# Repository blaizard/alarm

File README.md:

# Aube

Beautiful. Simple. Smart.

Aube is a smart alarm clock. It will guide you from the time you touch your bed until you wake up and is here make it a pleasant experience.
Aube is 3 major ideas: a design, a light and a smart device. 

## How to build Aube

The prototype is based on a Raspberry Pi 3 with the official 7 inches touch screen.
To fully build Aube, you will need a 3d printer, electronic circuit knowledges and some time!

The source contains various directories:
- **casing**: Contains the 3d models to be printed in order to build the skeleton of Aube
- **fw**: The firmware written in C to be compiled and loaded to a Microchip SAMD21 Microcontroller
- **schematics**: The electronics to handle the LED lighting with proximity sensor and the other sensors
- **sw**: The GUI of the alarm clock, written in Vanilla-Javascript and some back-end in Python

## Why Aube?
Pronounced /ob/, it is the translation of “dawn” in French. Dawn is a peaceful and relaxing experience which Aube is here to recreate every morning.

## Features
These are the raw features of Aube:
- Stereo speakers
- White LED light to simulate sunlight (with adjustable intensity and color temperature) with hovering dimming
- Connectivity: Wi-Fi, Bluetooth and USB ports (1xUSB type-C and 2x USB type-B) for charging only
- High sensitivity microphone for sleep monitoring
- Temperature, humidity and pressure sensors
- Proximity sensor to light up the screen on proximate movements

## Design
Inspired by Nordic designs, Aube is simple, pure with straight lines and strong contrasts.
Additionally, the user can customize the design by selecting the wooden base material.

3D modelization of the casing of Aube, this contains all the necessary electronics.

## Light
Our well-being and mood throughout the day is largely influenced by the light we are exposed to. Aube incorporates a light made to mimic the natural sun light.
Both intensity and light temperature can vary from 6500K to 4500K to recreate at best the color temperature of the light. Fade in from 4500K to 6500K in the morning to wake up smoothly and staying at 5000K in the evening to read a book before switching off the light.

The light has capacitive hovering capability, which means, without touching the device and by simply passing your hand on top of Aube, one can dim in or out the light.

Extract of the LED lighting circuitry.

## Apps
A set of Apps are displayed on the main screen of the alarm clock to provide the user with a personalized dashboard. The layout and the Apps can be selected by the user and configured to fit customized needs.

The following describes the default Apps coming with Aube. They all come with various designs that can be selected to create a personalized experience.

## Clock
The clock is the essential application for an alarm clock. It’s core functionality is to provide accurate time but also notify the user on important times or dates.

Alarms can trigger an action or a chain of actions, for example, it can be configured to slowly dimm in the LED lights and play a music through Spotify. Or open the blind and start your coffee machine… anything combination of operation is possible and configurable.

Actions can be:
- Dimm in/out the embedded LED light
- Speak out a predefined message
- Trigger actions from any Apps available (Spotify with the Music Apps, Meeting in the morning with the Calendar Apps…)
- IFTTT support to trigger up to 500+ services

## Sleep
Monitor your sleep using the integrated high sensitivity microphone. Can connect to sleep monitor devices for more accurate results.

It will also record your sleep (if you like), and give you insights (if you woke up, moved or even snored) during your sleep.

## Weather
Give you up to date information of the local weather. It can also provide you with the right forecast for the day when combined with the alarm. Or simply configured to give you the next 5 days forecast for your next vacations trip.
In addition, the weather Apps connects to internal sensors to give you current and accurate information about the pressure, humidity, luminosity and temperature of the room.

## Calendar
Connected to your personal calendar, it will inform you about your next meetings in the morning, to make sure you never miss any of your appointments!

## News
Aube will inform you of the main news every morning or RSS feed you connect it too. I can also read you a digest of the news every morning as you wake up.

## Music
Connect it to your favorite music provider: Spotify, … and it will wake you up with your favorite playlist in the morning.

## Radio
The radio Apps can connect to any digital radio or podcasts through the web to give you the right information in the morning or before you go to bed.

## Baby Monitor
Check if your baby is sleeping well with the Baby Monitor. It connects to your third party wireless camera or baby monitor to give you the information you need to ensure your peace of mind before you fall asleep.

## Countdown
Cannot wait for your next vacation? Your birthday? or your old friend coming to town? The countdown Apps will inform you about the remaining days before an event happen.

# Phone charging
In addition, Aube comes with USB ports on the back made to charge your phone. Equipped with USB Type-B and the new USB Type-C port, you should not need any other piece of electronics on your night stand anymore.

# Open Source Framework
All Apps are built on a fixed but powerful API (Application Programming Interface). This enables anyone to interact with the core functionality of Aube and hence develop compatible applications. Opening Aube to developers brings unlimited possibilities.

The process is simple, one needs to download the SDK (Software Development Kit), and follow the tutorial to develop its own application.

The application development is extremely simple in order to give anyone the possibility to develop its own Apps. In addition, applications are developed in the most predominant programming language (Javascript) and hence can be coupled with a variety of existing modules to speed up development.

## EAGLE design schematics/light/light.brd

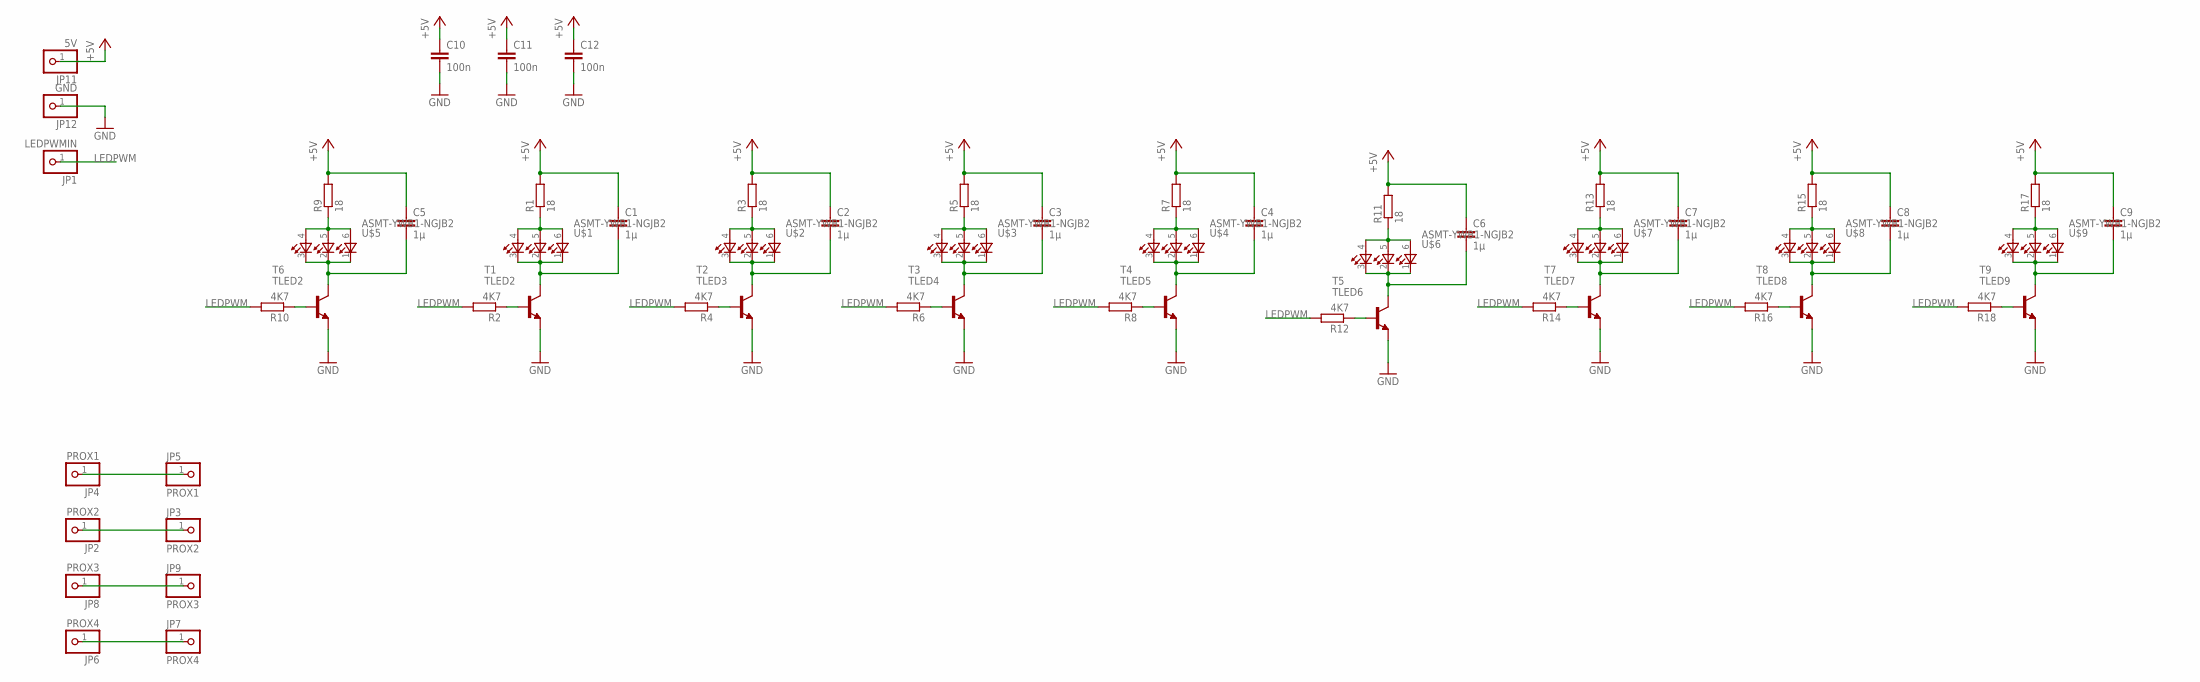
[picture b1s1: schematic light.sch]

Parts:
C1, C2, C3, C4, C5, C6, C7, C8, C9: 1µ; C0805
C10, C11, C12: 100n; C0805
JP1: LEDPWMIN; 1X01
JP2, JP3: PROX2; 1X01
JP4, JP5: PROX1; 1X01
JP6, JP7: PROX4; 1X01
JP8, JP9: PROX3; 1X01
JP11: 5V; 1X01
JP12: GND; 1X01
R1, R3, R5, R7, R9, R11, R13, R15, R17: 18; R0805
R2, R4, R6, R8, R10, R12, R14, R16, R18: 4K7; R0805
T1, T6: TLED2; SOT23-BEC
T2: TLED3; SOT23-BEC
T3: TLED4; SOT23-BEC
T4: TLED5; SOT23-BEC
T5: TLED6; SOT23-BEC
T7: TLED7; SOT23-BEC
T8: TLED8; SOT23-BEC
T9: TLED9; SOT23-BEC
U$1, U$2, U$3, U$4, U$5, U$6, U$7, U$8, U$9: ASMT-YWB1-NGJB2

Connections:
+5V: C1.1, C2.1, C3.1, C4.1, C5.1, C6.1, C7.1, C8.1, C9.1, C10.1, C11.1, C12.1, JP11.1, R1.2, R3.2, R5.2, R7.2, R9.2, R11.2, R13.2, R15.2, R17.2
BASE2: R12.1, T5.B
BASE3: R14.1, T7.B
BASE4: R16.1, T8.B
BASE5: R18.1, T9.B
COLLECTOR2: C6.2, T5.C, U$6.1, U$6.2, U$6.3
COLLECTOR3: C7.2, T7.C, U$7.1, U$7.2, U$7.3
COLLECTOR4: C8.2, T8.C, U$8.1, U$8.2, U$8.3
COLLECTOR5: C9.2, T9.C, U$9.1, U$9.2, U$9.3
GND: C10.2, C11.2, C12.2, JP12.1, T1.E, T2.E, T3.E, T4.E, T5.E, T6.E, T7.E, T8.E, T9.E
LEDPWM: JP1.1, R2.2, R4.2, R6.2, R8.2, R10.2, R12.2, R14.2, R16.2, R18.2
unnamed: R1.1, U$1.4, U$1.5, U$1.6
unnamed: C1.2, T1.C, U$1.1, U$1.2, U$1.3
unnamed: C2.2, T2.C, U$2.1, U$2.2, U$2.3
unnamed: R3.1, U$2.4, U$2.5, U$2.6
unnamed: R2.1, T1.B
unnamed: R4.1, T2.B
unnamed: C3.2, T3.C, U$3.1, U$3.2, U$3.3
unnamed: R5.1, U$3.4, U$3.5, U$3.6
unnamed: R6.1, T3.B
unnamed: C4.2, T4.C, U$4.1, U$4.2, U$4.3
unnamed: R7.1, U$4.4, U$4.5, U$4.6
unnamed: R8.1, T4.B
unnamed: R11.1, U$6.4, U$6.5, U$6.6
unnamed: C5.2, T6.C, U$5.1, U$5.2, U$5.3
unnamed: R13.1, U$7.4, U$7.5, U$7.6
unnamed: R15.1, U$8.4, U$8.5, U$8.6
unnamed: R17.1, U$9.4, U$9.5, U$9.6
unnamed: JP2.1, JP3.1
unnamed: JP4.1, JP5.1
unnamed: JP6.1, JP7.1
unnamed: JP8.1, JP9.1
unnamed: R9.1, U$5.4, U$5.5, U$5.6
unnamed: R10.1, T6.B

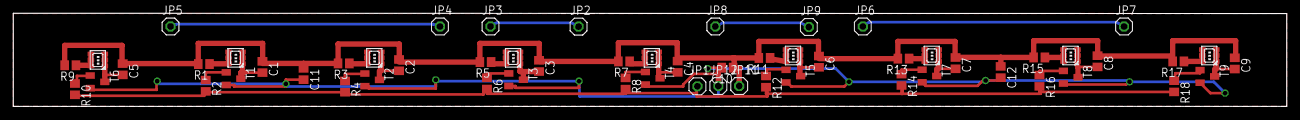
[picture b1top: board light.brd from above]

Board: 2 copper layers, 192.0 x 14.0 mm, 59 parts (0 on the bottom side), 34 nets.

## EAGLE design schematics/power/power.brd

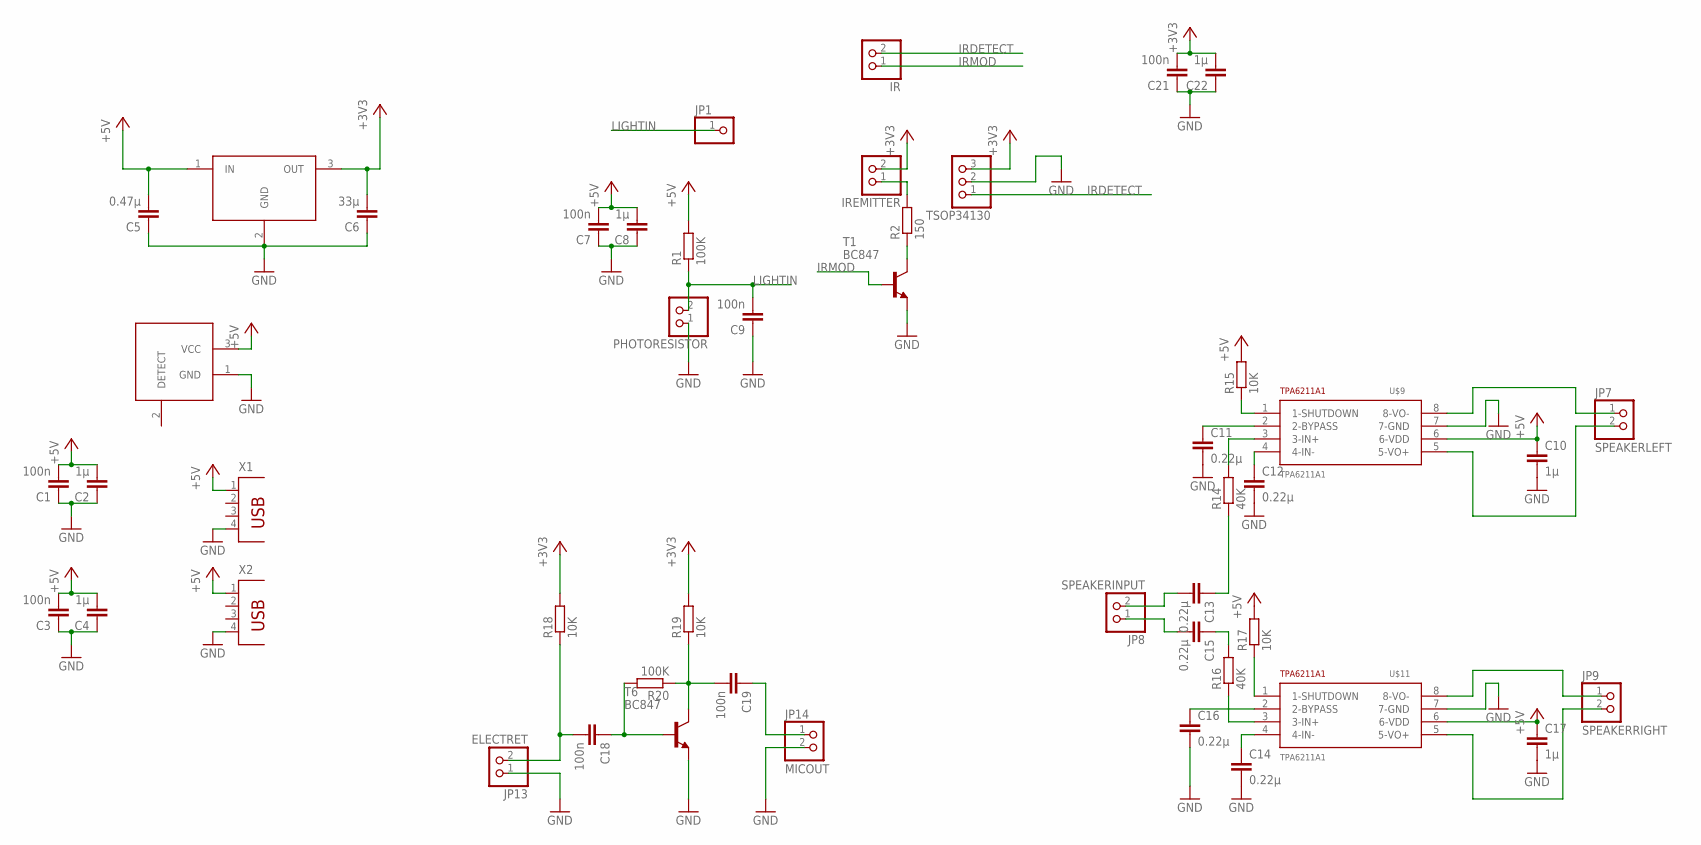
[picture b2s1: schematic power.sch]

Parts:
C1, C3, C7, C9, C18, C19, C21: 100n; C0805
C2, C4, C8, C10, C17, C22: 1µ; C0805
C5: 0.47µ; C0805
C6: 33µ; C0805
C11, C12, C13, C14, C15, C16: 0.22µ; C0805
IR: PINHD-1X2; 1X02
IREMITTER: PINHD-1X2; 1X02
JP1: PINHD-1X1; 1X01
JP7: SPEAKERLEFT; 1X02
JP8: SPEAKERINPUT; 1X02
JP9: SPEAKERRIGHT; 1X02
JP13: ELECTRET; 1X02
JP14: MICOUT; 1X02
PHOTORESISTOR: PINHD-1X2; 1X02
R1, R20: 100K; R0805
R2: 150; R0805
R14, R16: 40K; R0805
R15, R17, R18, R19: 10K; R0805
T1, T6: BC847; SOT23
TSOP34130: PINHD-1X3; 1X03
U$1: LM3940IMP-3.3; SOT223
U$2: POWERPLUG; DC10LPSOCKET
U$9, U$11: TPA6211A1; MSOP8
X1, X2: PN87520

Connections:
+3V3: C6.2, C21.2, C22.2, IREMITTER.2, R18.2, R19.2, TSOP34130.3, U$1.3 (OUT)
+5V: C1.2, C2.2, C3.2, C4.2, C5.2, C7.2, C8.2, C10.1, C17.1, R1.2, R15.2, R17.2, U$1.1 (IN), U$2.3 (VCC), U$9.6 (6-VDD), U$11.6 (6-VDD), X1.1, X2.1
GND: C1.1, C2.1, C3.1, C4.1, C5.1, C6.1, C7.1, C8.1, C9.1, C10.2, C11.2, C12.2, C14.2, C16.2, C17.2, C21.1, C22.1, JP13.1, JP14.2, PHOTORESISTOR.1, T1.2 (E), T6.2 (E), TSOP34130.2, U$1.2 (GND), U$2.1 (GND), U$9.7 (7-GND), U$11.7 (7-GND), X1.4, X2.4
IRDETECT: IR.2, TSOP34130.1
IRMOD: IR.1, T1.1 (B)
LIGHTIN: C9.2, JP1.1, PHOTORESISTOR.2, R1.1
unnamed: IREMITTER.1, R2.2
unnamed: R2.1, T1.3 (C)
unnamed: C13.1, R14.1
unnamed: C13.2, JP8.2
unnamed: JP7.1, U$9.8 (8-VO-)
unnamed: JP7.2, U$9.5 (5-VO+)
unnamed: C11.1, U$9.2 (2-BYPASS)
unnamed: C12.1, U$9.4 (4-IN-)
unnamed: R14.2, U$9.3 (3-IN+)
unnamed: C15.2, JP8.1
unnamed: C15.1, R16.2
unnamed: R15.1, U$9.1 (1-SHUTDOWN)
unnamed: R16.1, U$11.3 (3-IN+)
unnamed: C14.1, U$11.4 (4-IN-)
unnamed: C16.1, U$11.2 (2-BYPASS)
unnamed: R17.1, U$11.1 (1-SHUTDOWN)
unnamed: JP9.1, U$11.8 (8-VO-)
unnamed: JP9.2, U$11.5 (5-VO+)
unnamed: C19.2, R19.1, R20.1, T6.3 (C)
unnamed: C18.1, R20.2, T6.1 (B)
unnamed: C18.2, JP13.2, R18.1
unnamed: C19.1, JP14.1

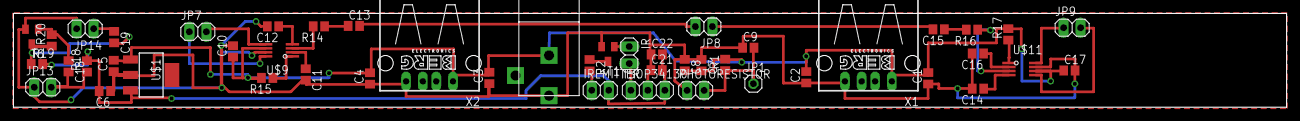
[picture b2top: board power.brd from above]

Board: 2 copper layers, 190.0 x 14.0 mm, 48 parts (0 on the bottom side), 28 nets.

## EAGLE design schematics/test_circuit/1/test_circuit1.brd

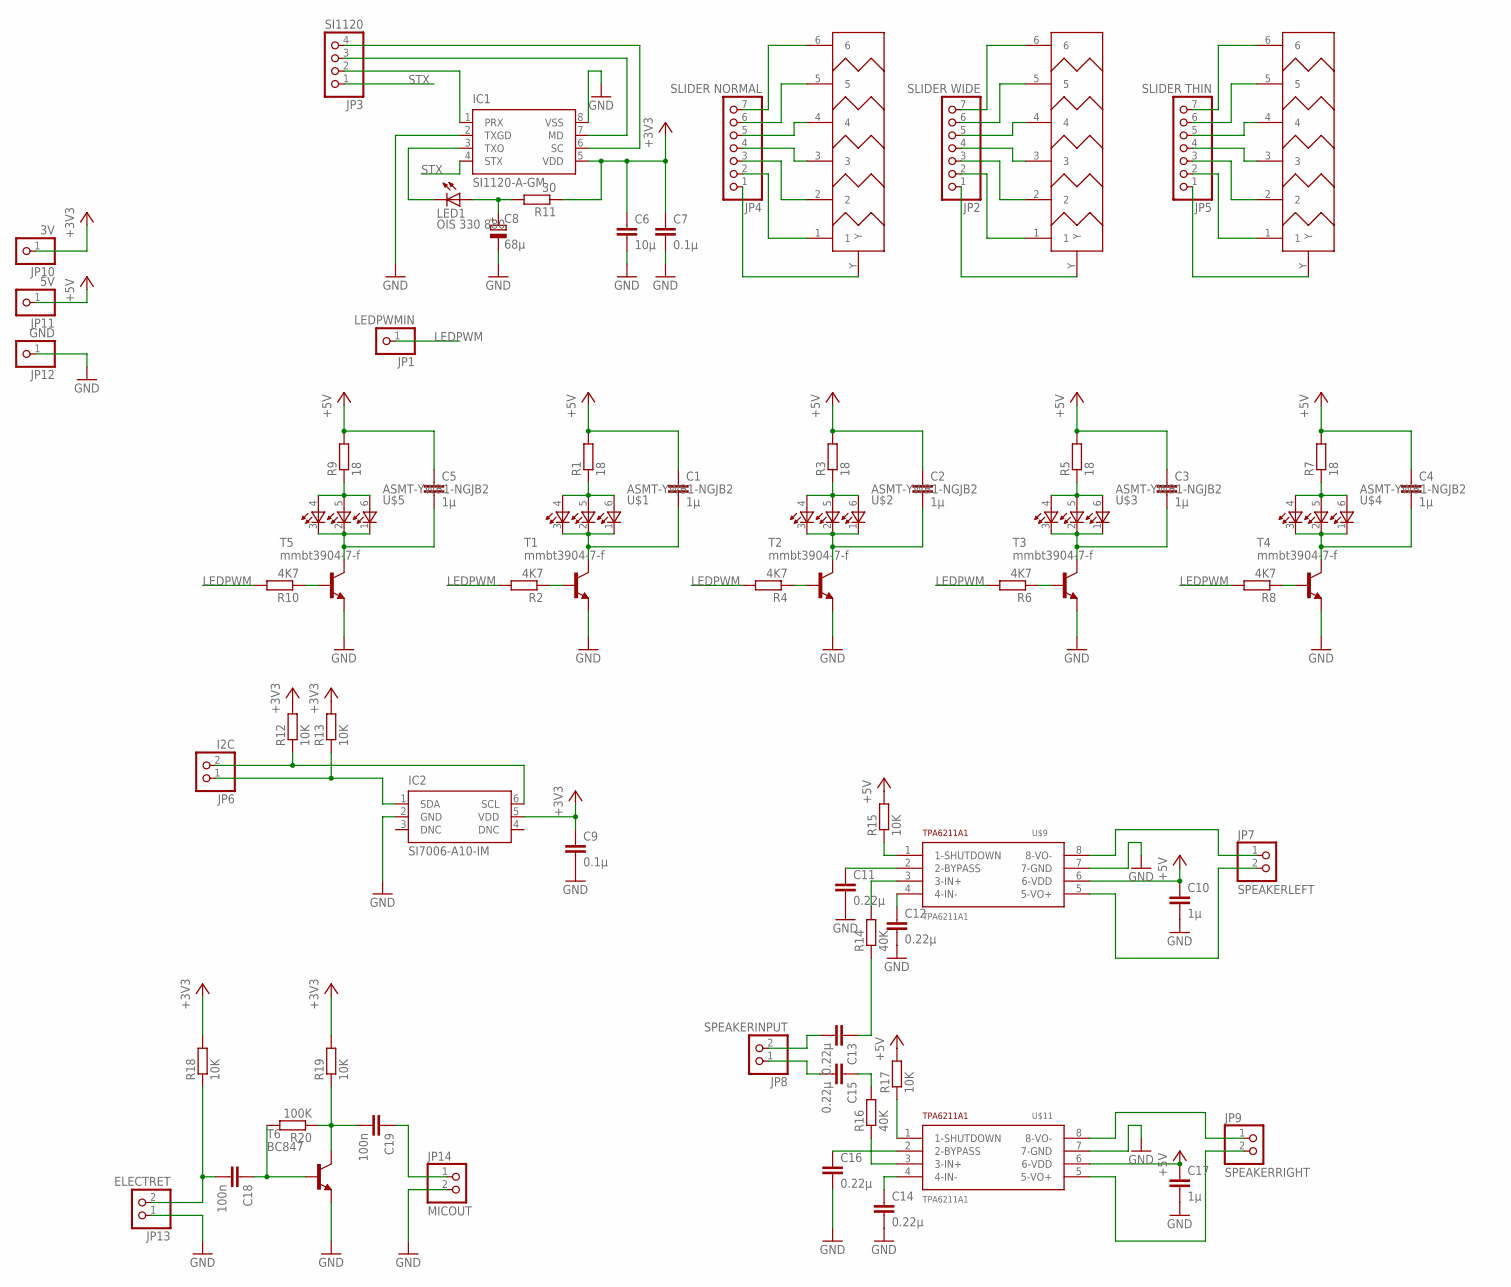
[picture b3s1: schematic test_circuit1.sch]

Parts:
C1, C2, C3, C4, C5, C10, C17: 1µ; C0805
C6: 10µ; C0805
C7, C9: 0.1µ; C0805
C8: 68µ; E2,5-7
C11, C12, C13, C14, C15, C16: 0.22µ; C0805
C18, C19: 100n; C0805
IC1: SI1120-A-GM; ODFN8-3X3
IC2: SI7006-A10-IM; DFN6-3X3
JP1: LEDPWMIN; 1X01
JP2: SLIDER WIDE; 1X07
JP3: SI1120; 1X04
JP4: SLIDER NORMAL; 1X07
JP5: SLIDER THIN; 1X07
JP6: I2C; 1X02
JP7: SPEAKERLEFT; 1X02
JP8: SPEAKERINPUT; 1X02
JP9: SPEAKERRIGHT; 1X02
JP10: 3V; 1X01
JP11: 5V; 1X01
JP12: GND; 1X01
JP13: ELECTRET; 1X02
JP14: MICOUT; 1X02
LED1: OIS 330 880; SML1206
R1, R3, R5, R7, R9: 18; R0805
R2, R4, R6, R8, R10: 4K7; R0805
R11: 30; R0805
R12, R13, R15, R17, R18, R19: 10K; R0805
R14, R16: 40K; R0805
R20: 100K; R0805
T1, T2, T3, T4, T5: mmbt3904-7-f; SOT23-EBC
T6: BC847; SOT23
U$1, U$2, U$3, U$4, U$5: ASMT-YWB1-NGJB2
U$6: SLIDER160MM_RESINT; SLIDER160MM_RI
U$7: SLIDER16MM_RESINT_WIDEY; SLIDER160MM_RI_WIDERY
U$8: SLIDER160MM_RESINT_THIN; SLIDER160MM_RI_THIN
U$9, U$11: TPA6211A1; MSOP8

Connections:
+3V3: C6.1, C7.1, C9.1, IC1.5 (VDD), IC2.5 (VDD), JP10.1, R11.1, R12.2, R13.2, R18.2, R19.2
+5V: C1.1, C2.1, C3.1, C4.1, C5.1, C10.1, C17.1, JP11.1, R1.2, R3.2, R5.2, R7.2, R9.2, R15.2, R17.2, U$9.6 (6-VDD), U$11.6 (6-VDD)
GND: C6.2, C7.2, C8.-, C9.2, C10.2, C11.2, C12.2, C14.2, C16.2, C17.2, IC1.2 (TXGD), IC1.8 (VSS), IC2.2 (GND), JP12.1, JP13.1, JP14.2, T1.E, T2.E, T3.E, T4.E, T5.E, T6.2 (E), U$9.7 (7-GND), U$11.7 (7-GND)
LEDPWM: JP1.1, R2.2, R4.2, R6.2, R8.2, R10.2
unnamed: R1.1, U$1.4, U$1.5, U$1.6
unnamed: C1.2, T1.C, U$1.1, U$1.2, U$1.3
unnamed: C2.2, T2.C, U$2.1, U$2.2, U$2.3
unnamed: R3.1, U$2.4, U$2.5, U$2.6
unnamed: R2.1, T1.B
unnamed: R4.1, T2.B
unnamed: C3.2, T3.C, U$3.1, U$3.2, U$3.3
unnamed: R5.1, U$3.4, U$3.5, U$3.6
unnamed: R6.1, T3.B
unnamed: C4.2, T4.C, U$4.1, U$4.2, U$4.3
unnamed: R7.1, U$4.4, U$4.5, U$4.6
unnamed: R8.1, T4.B
unnamed: C5.2, T5.C, U$5.1, U$5.2, U$5.3
unnamed: R9.1, U$5.4, U$5.5, U$5.6
unnamed: R10.1, T5.B
unnamed: JP4.7, U$6.6
unnamed: JP4.6, U$6.5
unnamed: JP4.5, U$6.4
unnamed: JP4.4, U$6.3
unnamed: JP4.3, U$6.2
unnamed: JP4.2, U$6.1
unnamed: IC1.3 (TXO), LED1.C
unnamed: C8.+, LED1.A, R11.2
unnamed: IC1.7 (MD), JP3.3
unnamed: IC1.6 (SC), JP3.4
unnamed: IC1.1 (PRX), JP3.2
unnamed: JP4.1, U$6.Y
unnamed: JP2.7, U$7.6
unnamed: JP2.6, U$7.5
unnamed: JP2.5, U$7.4
unnamed: JP2.4, U$7.3
unnamed: JP2.3, U$7.2
unnamed: JP2.2, U$7.1
unnamed: JP2.1, U$7.Y
unnamed: JP5.7, U$8.6
unnamed: JP5.6, U$8.5
unnamed: JP5.5, U$8.4
unnamed: JP5.4, U$8.3
unnamed: JP5.3, U$8.2
unnamed: JP5.2, U$8.1
unnamed: JP5.1, U$8.Y
unnamed: C13.1, R14.1
unnamed: C13.2, JP8.2
unnamed: IC2.6 (SCL), JP6.2, R12.1
unnamed: IC2.1 (SDA), JP6.1, R13.1
unnamed: JP7.1, U$9.8 (8-VO-)
unnamed: JP7.2, U$9.5 (5-VO+)
unnamed: C11.1, U$9.2 (2-BYPASS)
unnamed: C12.1, U$9.4 (4-IN-)
unnamed: R14.2, U$9.3 (3-IN+)
unnamed: C15.2, JP8.1
unnamed: C15.1, R16.2
unnamed: R15.1, U$9.1 (1-SHUTDOWN)
unnamed: R16.1, U$11.3 (3-IN+)
unnamed: C14.1, U$11.4 (4-IN-)
unnamed: C16.1, U$11.2 (2-BYPASS)
unnamed: R17.1, U$11.1 (1-SHUTDOWN)
unnamed: JP9.1, U$11.8 (8-VO-)
unnamed: JP9.2, U$11.5 (5-VO+)
unnamed: C19.2, R19.1, R20.1, T6.3 (C)
unnamed: C18.1, R20.2, T6.1 (B)
unnamed: C18.2, JP13.2, R18.1
unnamed: C19.1, JP14.1
STX: IC1.4 (STX), JP3.1

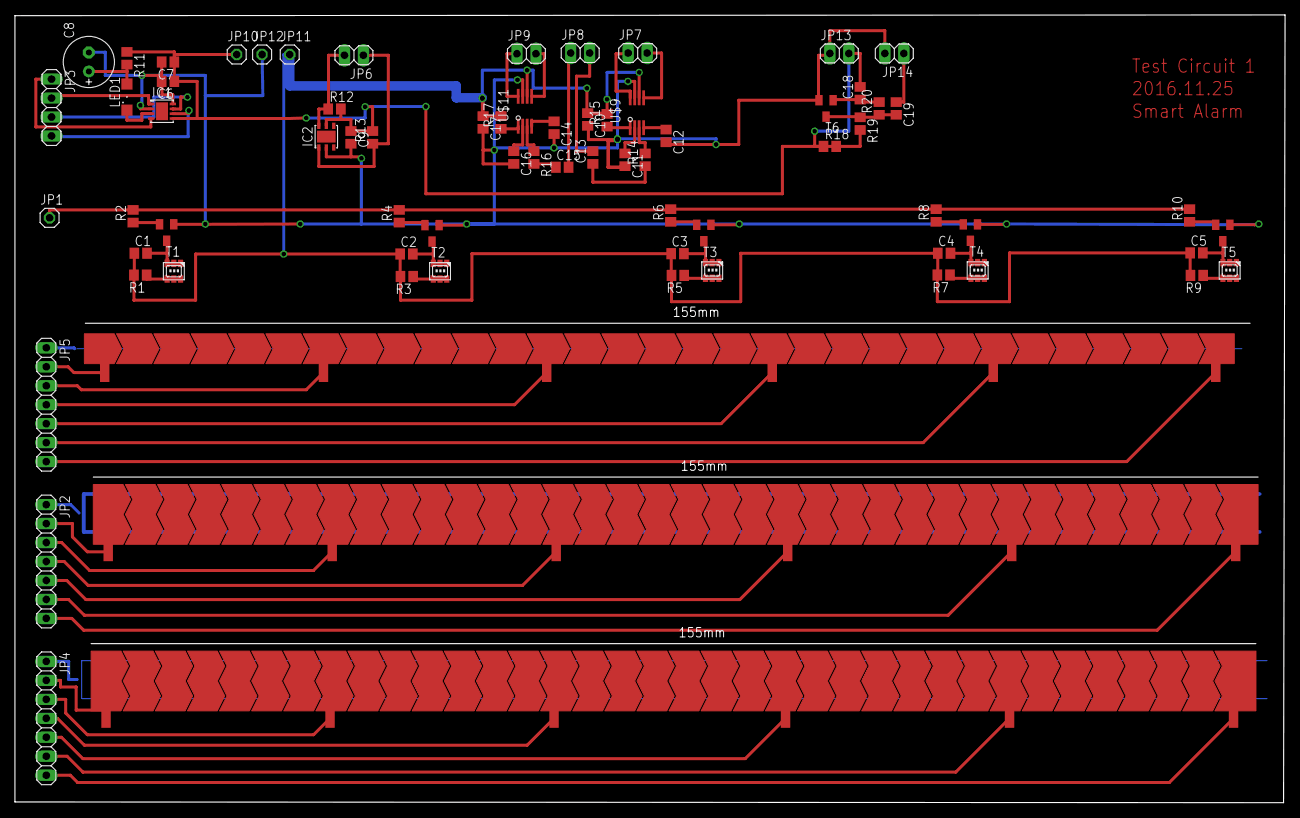
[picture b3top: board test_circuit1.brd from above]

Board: 2 copper layers, 170.0 x 105.4 mm, 72 parts (0 on the bottom side), 68 nets.

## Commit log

2017-03-12 First version of the case
2017-03-12 First version of the software
2017-03-15 Lighting board
2017-03-24 New update
2017-09-20 Initial version
2017-10-05 Added new weather module
2018-01-14 Major update Y
2018-01-14 Removed useless stuffs Y
2018-01-17 Added some documentation
2018-01-17 More documentation
2018-01-17 Moved How to build on top
2018-01-17 Adding images
2018-01-17 Reduced gif size

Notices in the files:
parts and their libraries:
si11xx_10: (c) 2014 Samuel Lourenço
